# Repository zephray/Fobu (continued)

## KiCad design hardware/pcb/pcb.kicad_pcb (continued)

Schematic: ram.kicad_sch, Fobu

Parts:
C300, C301, C310, C311: 470nF; C_0201_0603Metric
C302: 10uF; C_0402_1005Metric
C303, C304, C305, C306, C307, C308, C309: 100nF; C_0201_0603Metric
R300, R302: 10K; R_0402_1005Metric
R301: 0; R_0402_1005Metric
U300, U303: IS66WVC4M16-ALL; BGA-54_6x9_6.0x8.0mm
U301: MT48H16M32LFB5-6 or IS42VM32160E-6 or W989D2DBJX6; BGA-90_9x15_8.0x13.0mm
U302, U304: 74LVC1G126; SOT-353_SC-70-5

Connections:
+1V8: C302.1, C303.1, C304.1, C305.1, C306.1, C307.1, C308.1, C309.1, U301.A7 (VDD), U301.B2 (VDDQ), U301.B7 (VDDQ), U301.C9 (VDDQ), U301.D9 (VDDQ), U301.E1 (VDDQ), U301.F9 (VDD), U301.L1 (VDDQ), U301.L7 (VDD), U301.M9 (VDDQ), U301.N9 (VDDQ), U301.P2 (VDDQ), U301.P7 (VDDQ), U301.R7 (VDD); also elsewhere on the board
+RAM: C300.1, C301.1, C310.1, C311.1, R300.1, R302.1, U300.D6 (VDD), U300.E1 (VDDQ), U302.5 (VCC), U303.D6 (VDD), U303.E1 (VDDQ), U304.5 (VCC); also elsewhere on the board
CRAMA_A0: U300.A3 (A0); also elsewhere on the board
CRAMA_A1: U300.A4 (A1); also elsewhere on the board
CRAMA_A2: U300.A5 (A2); also elsewhere on the board
CRAMA_A3: U300.B3 (A3); also elsewhere on the board
CRAMA_A4: U300.B4 (A4); also elsewhere on the board
CRAMA_A5: U300.C3 (A5); also elsewhere on the board
CRAMA_A6: U300.C4 (A6); also elsewhere on the board
CRAMA_A7: U300.D4 (A7); also elsewhere on the board
CRAMA_A8: U300.H2 (A8); also elsewhere on the board
CRAMA_A9: U300.H3 (A9); also elsewhere on the board
CRAMA_A10: U300.H4 (A10); also elsewhere on the board
CRAMA_A11: U300.H5 (A11); also elsewhere on the board
CRAMA_A12: U300.G3 (A12); also elsewhere on the board
CRAMA_A13: U300.G4 (A13); also elsewhere on the board
CRAMA_A14: U300.F3 (A14); also elsewhere on the board
CRAMA_A15: U300.F4 (A15); also elsewhere on the board
CRAMA_A16: U300.E4 (A16); also elsewhere on the board
CRAMA_A17: U300.D3 (A17); also elsewhere on the board
CRAMA_A18: U300.H1 (A18); also elsewhere on the board
CRAMA_A19: U300.G2 (A19); also elsewhere on the board
CRAMA_A20: U300.H6 (A20); also elsewhere on the board
CRAMA_A21: U300.E3 (A21); also elsewhere on the board
CRAMA_ADVN: U300.J3 (~ADV); also elsewhere on the board
CRAMA_CEN: U302.2; also elsewhere on the board
CRAMA_CLK: U300.J2 (CLK); also elsewhere on the board
CRAMA_CRE: U300.A6 (CRE); also elsewhere on the board
CRAMA_DQ0: U300.B6 (DQ0); also elsewhere on the board
CRAMA_DQ1: U300.C5 (DQ1); also elsewhere on the board
CRAMA_DQ2: U300.C6 (DQ2); also elsewhere on the board
CRAMA_DQ3: U300.D5 (DQ3); also elsewhere on the board
CRAMA_DQ4: U300.E5 (DQ4); also elsewhere on the board
CRAMA_DQ5: U300.F5 (DQ5); also elsewhere on the board
CRAMA_DQ6: U300.F6 (DQ6); also elsewhere on the board
CRAMA_DQ7: U300.G6 (DQ7); also elsewhere on the board
CRAMA_DQ8: U300.B1 (DQ8); also elsewhere on the board
CRAMA_DQ9: U300.C1 (DQ9); also elsewhere on the board
CRAMA_DQ10: U300.C2 (DQ10); also elsewhere on the board
CRAMA_DQ11: U300.D2 (DQ11); also elsewhere on the board
CRAMA_DQ12: U300.E2 (DQ12); also elsewhere on the board
CRAMA_DQ13: U300.F2 (DQ13); also elsewhere on the board
CRAMA_DQ14: U300.F1 (DQ14); also elsewhere on the board
CRAMA_DQ15: U300.G1 (DQ15); also elsewhere on the board
CRAMA_LBN: U300.A1 (~LB); also elsewhere on the board
CRAMA_OEN: U300.A2 (~OE); also elsewhere on the board
CRAMA_UBN: U300.B2 (~UB); also elsewhere on the board
CRAMA_WAIT: U300.J1 (WAIT); also elsewhere on the board
CRAMA_WEN: U300.G5 (~WE); also elsewhere on the board
CRAMB_A0: U303.A3 (A0); also elsewhere on the board
CRAMB_A1: U303.A4 (A1); also elsewhere on the board
CRAMB_A2: U303.A5 (A2); also elsewhere on the board
CRAMB_A3: U303.B3 (A3); also elsewhere on the board
CRAMB_A4: U303.B4 (A4); also elsewhere on the board
CRAMB_A5: U303.C3 (A5); also elsewhere on the board
CRAMB_A6: U303.C4 (A6); also elsewhere on the board
CRAMB_A7: U303.D4 (A7); also elsewhere on the board
CRAMB_A8: U303.H2 (A8); also elsewhere on the board
CRAMB_A9: U303.H3 (A9); also elsewhere on the board
CRAMB_A10: U303.H4 (A10); also elsewhere on the board
CRAMB_A11: U303.H5 (A11); also elsewhere on the board
CRAMB_A12: U303.G3 (A12); also elsewhere on the board
CRAMB_A13: U303.G4 (A13); also elsewhere on the board
CRAMB_A14: U303.F3 (A14); also elsewhere on the board
CRAMB_A15: U303.F4 (A15); also elsewhere on the board
CRAMB_A16: U303.E4 (A16); also elsewhere on the board
CRAMB_A17: U303.D3 (A17); also elsewhere on the board
CRAMB_A18: U303.H1 (A18); also elsewhere on the board
CRAMB_A19: U303.G2 (A19); also elsewhere on the board
CRAMB_A20: U303.H6 (A20); also elsewhere on the board
CRAMB_A21: U303.E3 (A21); also elsewhere on the board
CRAMB_ADVN: U303.J3 (~ADV); also elsewhere on the board
CRAMB_CEN: U304.2; also elsewhere on the board
CRAMB_CLK: U303.J2 (CLK); also elsewhere on the board
CRAMB_CRE: U303.A6 (CRE); also elsewhere on the board
CRAMB_DQ0: U303.B6 (DQ0); also elsewhere on the board
CRAMB_DQ1: U303.C5 (DQ1); also elsewhere on the board
CRAMB_DQ2: U303.C6 (DQ2); also elsewhere on the board
CRAMB_DQ3: U303.D5 (DQ3); also elsewhere on the board
CRAMB_DQ4: U303.E5 (DQ4); also elsewhere on the board
CRAMB_DQ5: U303.F5 (DQ5); also elsewhere on the board
CRAMB_DQ6: U303.F6 (DQ6); also elsewhere on the board
CRAMB_DQ7: U303.G6 (DQ7); also elsewhere on the board
CRAMB_DQ8: U303.B1 (DQ8); also elsewhere on the board
CRAMB_DQ9: U303.C1 (DQ9); also elsewhere on the board
CRAMB_DQ10: U303.C2 (DQ10); also elsewhere on the board
CRAMB_DQ11: U303.D2 (DQ11); also elsewhere on the board
CRAMB_DQ12: U303.E2 (DQ12); also elsewhere on the board
CRAMB_DQ13: U303.F2 (DQ13); also elsewhere on the board
CRAMB_DQ14: U303.F1 (DQ14); also elsewhere on the board
CRAMB_DQ15: U303.G1 (DQ15); also elsewhere on the board
CRAMB_LBN: U303.A1 (~LB); also elsewhere on the board
CRAMB_OEN: U303.A2 (~OE); also elsewhere on the board
CRAMB_UBN: U303.B2 (~UB); also elsewhere on the board
CRAMB_WAIT: U303.J1 (WAIT); also elsewhere on the board
CRAMB_WEN: U303.G5 (~WE); also elsewhere on the board
FPGA_RAM_EN: U302.1, U304.1
GND: C300.2, C301.2, C302.2, C303.2, C304.2, C305.2, C306.2, C307.2, C308.2, C309.2, C310.2, C311.2, U300.D1 (VSSQ), U300.E6 (VSS), U301.A3 (VSS), U301.B3 (VSSQ), U301.B8 (VSSQ), U301.C1 (VSSQ), U301.D1 (VSSQ), U301.E9 (VSSQ), U301.F1 (VSS), U301.L3 (VSS), U301.L9 (VSSQ), U301.M1 (VSSQ), U301.N1 (VSSQ), U301.P3 (VSSQ), U301.P8 (VSSQ), U301.R3 (VSS), U302.3 (GND), U303.D1 (VSSQ), U303.E6 (VSS), U304.3 (GND); also elsewhere on the board
unnamed: R300.2, U300.B5 (~CE), U302.4
unnamed: R301.2, U301.J1 (CLK)
unnamed: R302.2, U303.B5 (~CE), U304.4
SDRAM_A0: U301.G8 (A0); also elsewhere on the board
SDRAM_A1: U301.G9 (A1); also elsewhere on the board
SDRAM_A2: U301.F7 (A2); also elsewhere on the board
SDRAM_A3: U301.F3 (A3); also elsewhere on the board
SDRAM_A4: U301.G1 (A4); also elsewhere on the board
SDRAM_A5: U301.G2 (A5); also elsewhere on the board
SDRAM_A6: U301.G3 (A6); also elsewhere on the board
SDRAM_A7: U301.H1 (A7); also elsewhere on the board
SDRAM_A8: U301.H2 (A8); also elsewhere on the board
SDRAM_A9: U301.J3 (A9); also elsewhere on the board
SDRAM_A10: U301.G7 (A10); also elsewhere on the board
SDRAM_A11: U301.H9 (A11); also elsewhere on the board
SDRAM_A12: U301.H3 (A12); also elsewhere on the board
SDRAM_BA0: U301.J7 (BA0); also elsewhere on the board
SDRAM_BA1: U301.H8 (BA1); also elsewhere on the board
SDRAM_CAS: U301.K7 (~CAS); also elsewhere on the board
SDRAM_CKE: U301.J2 (CKE); also elsewhere on the board
SDRAM_CLK: R301.1; also elsewhere on the board
SDRAM_CS0: U301.J8 (~CS); also elsewhere on the board
SDRAM_D0: U301.R8 (DQ0); also elsewhere on the board
SDRAM_D1: U301.N7 (DQ1); also elsewhere on the board
SDRAM_D2: U301.R9 (DQ2); also elsewhere on the board
SDRAM_D3: U301.N8 (DQ3); also elsewhere on the board
SDRAM_D4: U301.P9 (DQ4); also elsewhere on the board
SDRAM_D5: U301.M8 (DQ5); also elsewhere on the board
SDRAM_D6: U301.M7 (DQ6); also elsewhere on the board
SDRAM_D7: U301.L8 (DQ7); also elsewhere on the board
SDRAM_D8: U301.L2 (DQ8); also elsewhere on the board
SDRAM_D9: U301.M3 (DQ9); also elsewhere on the board
SDRAM_D10: U301.M2 (DQ10); also elsewhere on the board
SDRAM_D11: U301.P1 (DQ11); also elsewhere on the board
SDRAM_D12: U301.N2 (DQ12); also elsewhere on the board
SDRAM_D13: U301.R1 (DQ13); also elsewhere on the board
SDRAM_D14: U301.N3 (DQ14); also elsewhere on the board
SDRAM_D15: U301.R2 (DQ15); also elsewhere on the board
SDRAM_D16: U301.E8 (DQ16); also elsewhere on the board
SDRAM_D17: U301.D7 (DQ17); also elsewhere on the board
SDRAM_D18: U301.D8 (DQ18); also elsewhere on the board
SDRAM_D19: U301.B9 (DQ19); also elsewhere on the board
SDRAM_D20: U301.C8 (DQ20); also elsewhere on the board
SDRAM_D21: U301.A9 (DQ21); also elsewhere on the board
SDRAM_D22: U301.C7 (DQ22); also elsewhere on the board
SDRAM_D23: U301.A8 (DQ23); also elsewhere on the board
SDRAM_D24: U301.A2 (DQ24); also elsewhere on the board
SDRAM_D25: U301.C3 (DQ25); also elsewhere on the board
SDRAM_D26: U301.A1 (DQ26); also elsewhere on the board
SDRAM_D27: U301.C2 (DQ27); also elsewhere on the board
SDRAM_D28: U301.B1 (DQ28); also elsewhere on the board
SDRAM_D29: U301.D2 (DQ29); also elsewhere on the board
SDRAM_D30: U301.D3 (DQ30); also elsewhere on the board
SDRAM_D31: U301.E2 (DQ31); also elsewhere on the board
SDRAM_DM0: U301.K9 (DQM0); also elsewhere on the board
SDRAM_DM1: U301.K1 (DQM1); also elsewhere on the board
SDRAM_DM2: U301.F8 (DQM2); also elsewhere on the board
SDRAM_DM3: U301.F2 (DQM3); also elsewhere on the board
SDRAM_RAS: U301.J9 (~RAS); also elsewhere on the board
SDRAM_WE: U301.K8 (~WE); also elsewhere on the board

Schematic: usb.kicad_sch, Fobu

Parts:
C800: 470nF; C_0201_0603Metric
C801, C805, C808, C811, C814: 1uF; C_0402_1005Metric
C802, C803, C804, C806, C807, C810, C812, C813, C815, C816, C817, C818, C819, C820, C821, C822, C827, C828, C838: 100nF; C_0201_0603Metric
C837: 10uF; C_0402_1005Metric
J800: USB_C_Receptacle; USB_C_Receptacle_Amphenol_12401548E4-2A
L800: EXC14CE900U; L_CommonModeChoke_Panasonic_EXC14CE
L801, L802: 300R; L_0603_1608Metric
L803, L804, L805, L806, L807: 120R; L_0402_1005Metric
R800, R802: 10K; C_0402_1005Metric
R801: 3K/1%; C_0402_1005Metric
U800: USBLC6-2P6; SOT-666
U801: FUSB302UCX; WLP-9_1.448x1.468mm_Layout3x3_P0.4mm_Ball0.27mm_Pad0.25mm
U802: CBTL08GP053; BGA-40_6x9_3.5x5.0mm
U803: TC358777; BGA-80_10x10_7.0x7.0mm
X800: 19.2MHz; Oscillator_SMD_Abracon_ASE-4Pin_3.2x2.5mm

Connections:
+1V2_DP: L804.1, L805.1, L806.1, L807.1; also elsewhere on the board
+1V8_DP: C800.2, L803.2, R800.1, R802.1, X800.4 (Vdd); also elsewhere on the board
+3V3: C817.1, C818.1, C838.1, U801.A3 (VDD), U801.B1 (VCONN), U802.B2 (VDD), U802.E3 (VDD), U802.E4 (VDDIO), U802.H3 (VDDIO), U802.J5 (SW_EN); also elsewhere on the board
/usb/TYPEC_DN: J800.A7 (D-), J800.B7 (D-), L800.4, U800.3 (I/O2), U800.4 (I/O2)
/usb/TYPEC_DP: J800.A6 (D+), J800.B6 (D+), L800.3, U800.1 (I/O1), U800.6 (I/O1)
/usb/TYPEC_RX1N: J800.B10 (RX1-), U802.J6 (OP1-)
/usb/TYPEC_RX1P: J800.B11 (RX1+), U802.H6 (OP1+)
/usb/TYPEC_RX2N: J800.A10 (RX2-), U802.E6 (OP2-)
/usb/TYPEC_RX2P: J800.A11 (RX2+), U802.D6 (OP2+)
/usb/TYPEC_SBU1: J800.A8 (SBU1), U802.A5 (OP5A)
/usb/TYPEC_SBU2: J800.B8 (SBU2), U802.A6 (OP5B)
/usb/TYPEC_TX1N: J800.A3 (TX1-), U802.F6 (OP3-)
/usb/TYPEC_TX1P: J800.A2 (TX1+), U802.G6 (OP3+)
/usb/TYPEC_TX2N: J800.B3 (TX2-), U802.B6 (OP4-)
/usb/TYPEC_TX2P: J800.B2 (TX2+), U802.C6 (OP4+)
DP_HPD: U803.H9 (HPD)
DP_RST: U803.B10 (RESX)
GND: C800.1, C801.2, C802.2, C803.2, C804.2, C805.2, C806.2, C807.2, C808.2, C810.2, C811.2, C812.2, C813.2, C814.2, C815.2, C816.2, C817.2, C818.2, C837.2, C838.2, J800.A1 (GND), J800.A12 (GND), J800.B1 (GND), J800.B12 (GND), L801.2, U800.2 (GND), U801.C2 (GND), U802.B1 (IP5-), U802.B3 (IP8A), U802.B4 (IP8B), U802.B5 (GND), U802.C1 (IP5+), U802.D1 (IP4-), U802.D3 (GND), U802.D4 (SLV_ADDR2), U802.E1 (IP4+), U802.F3 (GND), U802.F4 (GND), U802.H1 (IP2+), U802.H2 (GND), U802.H5 (SLV_ADDR1), U802.J1 (IP2-), U802.J2 (IP1+), U802.J3 (IP1-), U803.A4 (DSI1_DM3), U803.A5 (DSI1_DM2), U803.A6 (DSI1_CM), U803.A8 (DSI1_DM1), U803.A9 (DSI1_DM0), U803.B3 (VSS), U803.B4 (DSI1_DP3), U803.B5 (DSI1_DP2), U803.B6 (DSI1_CP), U803.B7 (VSS), U803.B8 (DSI1_DP1), U803.B9 (DSI1_DP0), U803.D1 (DSI0_DM2), U803.D2 (DSI0_DP2), U803.D4 (TEST5), U803.D5 (TEST6), U803.D6 (TEST7), U803.D7 (TEST1), U803.D9 (SPI_SS_I2C_ADR_SEL), U803.E1 (DSI0_DM3), U803.E2 (DSI0_DP3), U803.E4 (VSS), U803.E5 (TEST3), U803.E6 (TEST4), U803.E7 (VPGM), U803.F2 (VSS), U803.F4 (TEST9), U803.F5 (VSS), U803.F6 (TEST8), U803.G4 (DIFF_SE), U803.G5 (TEST2), U803.G6 (TEST10), U803.G7 (VSS), U803.G9 (SPI_I2C), U803.H2 (VSS), U803.J2 (VSS_DP), U803.J4 (VSS_DP), U803.J6 (VSS_DP), U803.J8 (VSS_DP), X800.2 (GND); also elsewhere on the board
I2C3_SCL: U801.B3 (SCL), U802.H4 (I2C_SDA); also elsewhere on the board
I2C3_SDA: U801.C3 (SDA), U802.J4 (I2C_CLK); also elsewhere on the board
I2C4_SCL: U803.C9 (SPI_SCK/I2C_SCL); also elsewhere on the board
I2C4_SDA: U803.D10 (SPI_MOSI/I2C_SDA); also elsewhere on the board
MIPI_CKN: U803.C2 (DSI0_CP); also elsewhere on the board
MIPI_CKP: U803.C1 (DSI0_CM); also elsewhere on the board
MIPI_D0N: U803.A2 (DSI0_DP0); also elsewhere on the board
MIPI_D0P: U803.A1 (DSI0_DM0); also elsewhere on the board
MIPI_D1N: U803.B1 (DSI0_DM1); also elsewhere on the board
MIPI_D1P: U803.B2 (DSI0_DP1); also elsewhere on the board
unnamed: C801.1, C802.1, C803.1, C804.1, L803.1, U803.A10 (VDD_IO), U803.K1 (VDD_PLL18), U803.K4 (VDD_DP18), U803.K8 (VDD_DP18)
unnamed: C805.1, C806.1, C807.1, L804.2, U803.F1 (VDDC), U803.H1 (VDDC)
unnamed: C808.1, C810.1, L805.2, U803.H10 (VDD_PLL912)
unnamed: C811.1, C812.1, C813.1, L806.2, U803.J1 (VDD_DP12), U803.K6 (VDD_DP12)
unnamed: C814.1, C815.1, C816.1, L807.2, U803.A3 (VDD_DSI12), U803.A7 (VDD_DSI12)
unnamed: C819.1, U803.J3 (DP_P0)
unnamed: C819.2, U802.F1 (IP3+)
unnamed: C820.1, U803.K3 (DP_M0)
unnamed: C820.2, U802.G1 (IP3-)
unnamed: C821.1, U803.J5 (DP_P1)
unnamed: C821.2, U802.A1 (IP6+)
unnamed: C822.1, U803.K5 (DP_M1)
unnamed: C822.2, U802.A2 (IP6-)
unnamed: C827.1, U803.J10 (DP_AUXP)
unnamed: C827.2, U802.A3 (IP7A)
unnamed: C828.1, U803.K10 (DP_AUXM)
unnamed: C828.2, U802.A4 (IP7B)
unnamed: J800.A4 (VBUS), J800.A9 (VBUS), J800.B4 (VBUS), J800.B9 (VBUS), L802.2, U800.5 (VBUS), U801.A2 (VBUS)
unnamed: J800.A5 (CC1), U801.C1 (CC1)
unnamed: J800.B5 (CC2), U801.A1 (CC2)
unnamed: J800.S1 (SHIELD), L801.1
unnamed: R800.2, X800.1 (EN)
unnamed: R801.1, U803.G1 (PREC_RES0)
unnamed: R801.2, U803.G2 (PREC_RES1)
unnamed: R802.2, U803.F7 (DISABLE_ASSR)
unnamed: U803.K2 (REFCLK), X800.3 (OUT)
SAI1_MCLK: U803.E10 (I2S_OSCLK); also elsewhere on the board
SAI1_TX_BCLK: U803.F9 (I2S_BCLK); also elsewhere on the board
SAI1_TX_DATA0: U803.F10 (I2S_DATA); also elsewhere on the board
SAI1_TX_SYNC: U803.G10 (I2S_LRCLK); also elsewhere on the board
USB_DM: L800.1; also elsewhere on the board
USB_DP: L800.2; also elsewhere on the board
VBUS: C837.1, L802.1; also elsewhere on the board

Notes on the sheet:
Switch can be turned off by I2C

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
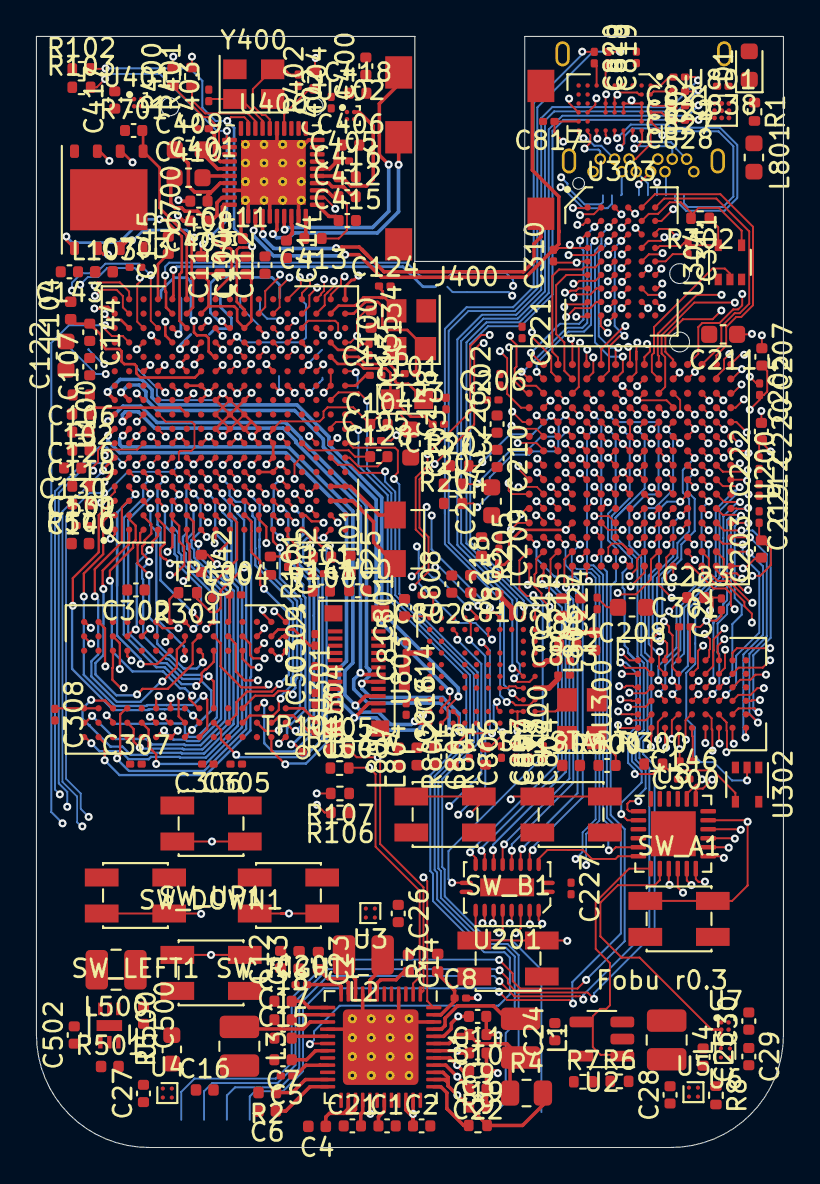
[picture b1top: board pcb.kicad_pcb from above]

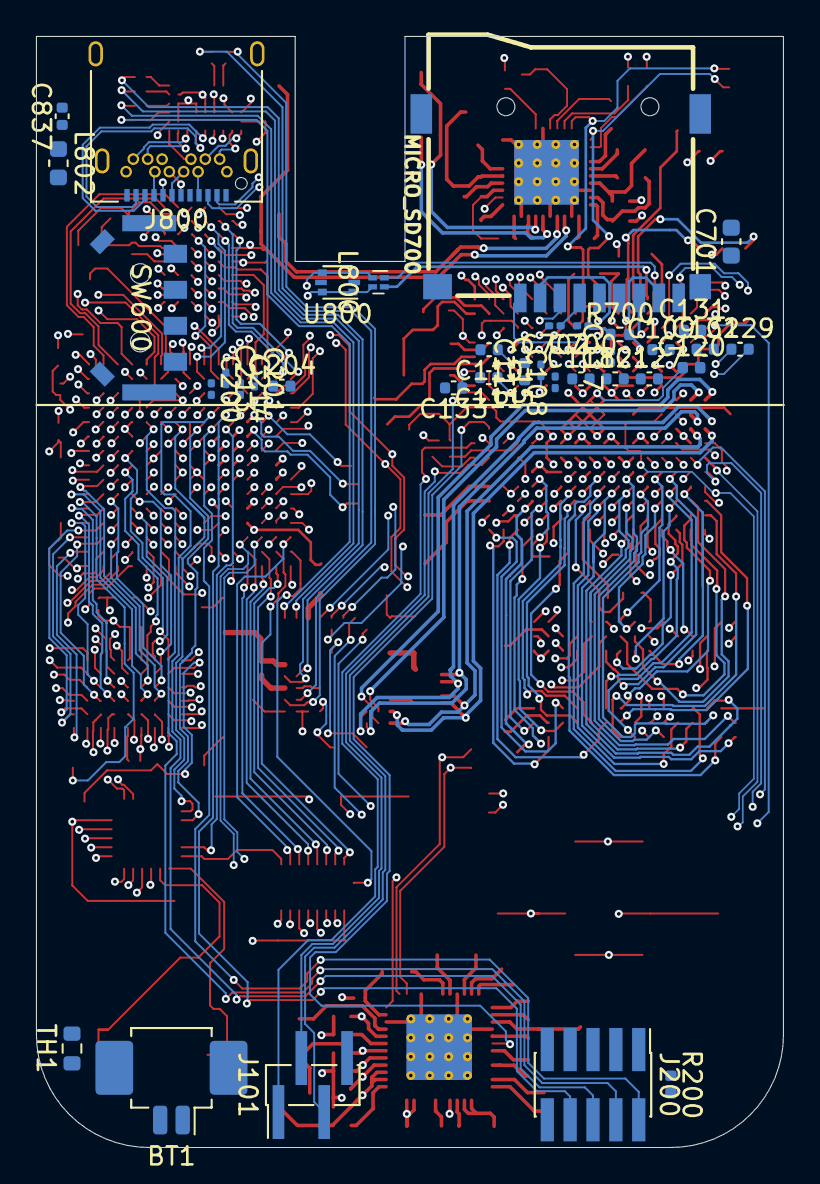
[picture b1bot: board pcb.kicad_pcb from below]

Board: 6 copper layers, 41.5 x 61.7 mm, 273 parts (36 on the bottom side), 369 nets.

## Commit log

2020-11-04 - Initial commit
2020-11-06 - Import lvgl - Update linux side OSAL to support lvgl
2020-11-06 - Fix lvgl set_text_vfmt va_list reuse
2020-11-07 - Sepearate home screen into an application
2020-12-31 - Implement home screen
2020-12-31 - Rename housekeeping task
2021-01-01 - Use fake double buffering in SDL
2021-02-18 - Initial wip hardware design
2021-02-27 - Migrate to KiCAD 5.99 nightly, pcb initial layout
2021-03-08 - Working on pcb layout
2021-03-13 - PCB r0.3 routed, need to finalize
2021-03-17 - PCB layout finished for r0p3
2021-04-22 fw: initial bring up
2021-04-22 - PCB: prepare for r0p4
2021-04-24 - fw: initial support for video output
2021-04-25 - fw: continue bring up on CM7
2021-12-19 - fw: fix source permissions
2022-03-19 - pcb: r0p4, update to KiCAD 6.0
